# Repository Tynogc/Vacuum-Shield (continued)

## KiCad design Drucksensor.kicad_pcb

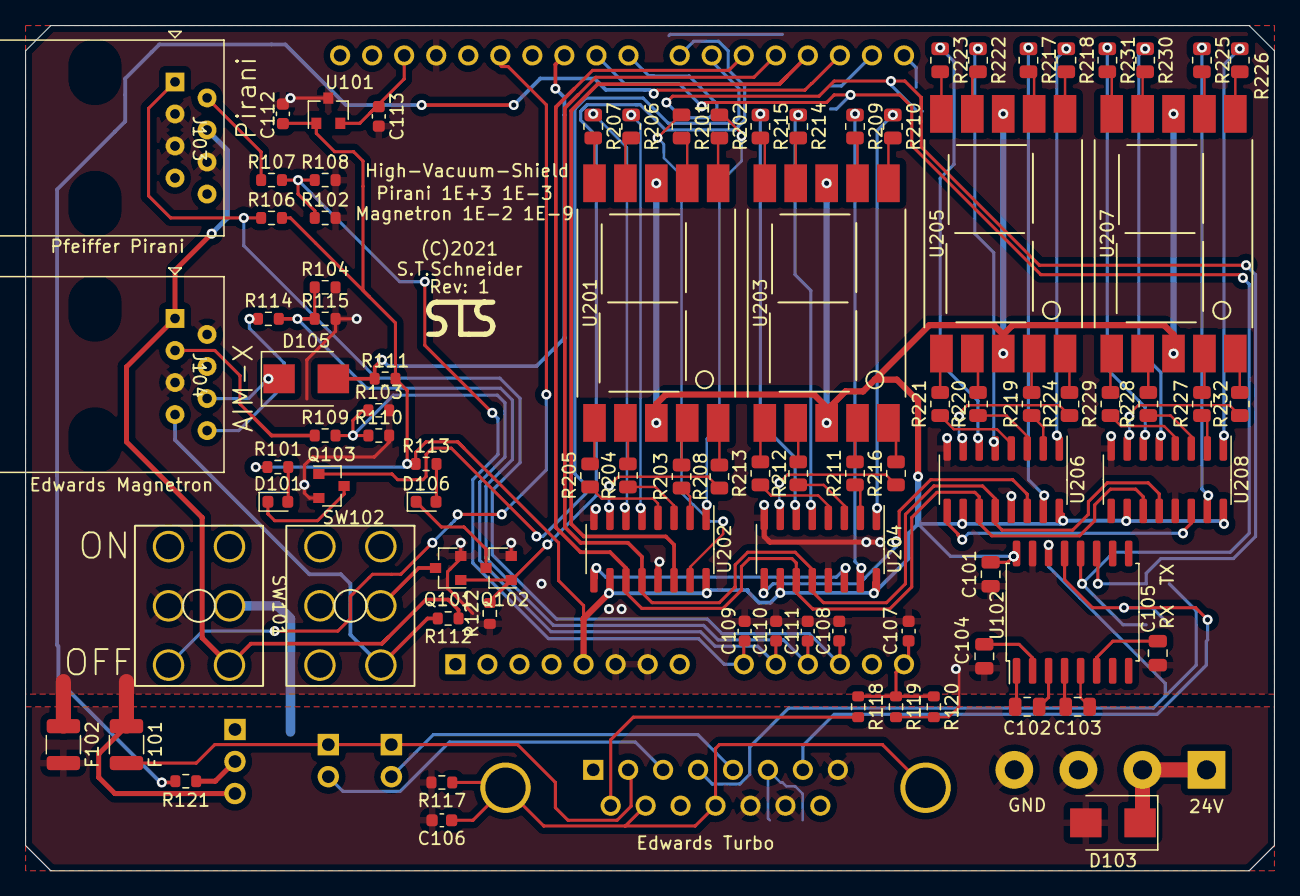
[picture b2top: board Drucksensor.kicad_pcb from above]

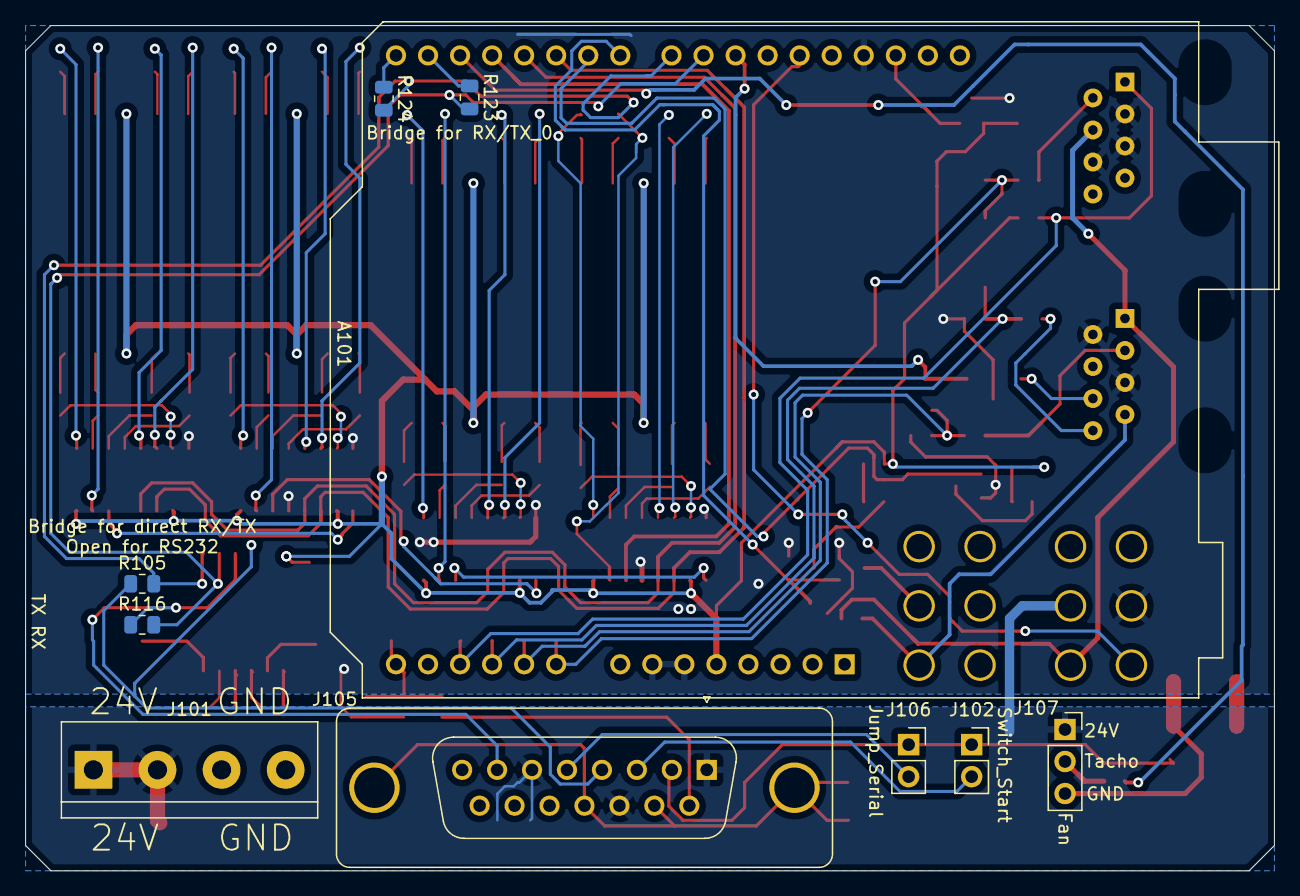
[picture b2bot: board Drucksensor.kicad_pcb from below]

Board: 2 copper layers, 99.0 x 67.0 mm, 98 parts (10 on the bottom side), 114 nets.

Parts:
A101: Arduino_UNO_R3
C101, C102, C103, C104, C105: 1µ 16V; C_0805_2012Metric
C106, C107, C108, C109, C110, C111, C112, C113: 100n; C_0603_1608Metric
D101, D106: grün; LED_0603_1608Metric
D103, D105: STPS340U; D_SMB
F101, F102: Fuse; R_1210_3225Metric
J101: Conn_01x02; TerminalBlock_bornier-4_P5.08mm
J102: Start; PinSocket_1x02_P2.54mm_Vertical
J103, J104: RJ45; RJ45_Amphenol_54602_mod
J105: DB15_Female_MountingHoles; DSUB-15_Female_Vertical_P2.77x2.84mm_MountingHoles
J106: Serial; PinSocket_1x02_P2.54mm_Vertical
J107: Conn_01x03_Male; PinSocket_1x03_P2.54mm_Vertical
Q101, Q102, Q103: Q_NMOS_GSD; SOT-23
R101, R113: 470; R_0603_1608Metric
R102, R103, R104, R106, R107, R108, R109, R110, R111, R114, R115, R118, R119, R120, R122: 10k; R_0603_1608Metric
R105, R116, R123, R124: Open; R_0805_2012Metric
R112: NC; R_0603_1608Metric
R117, R121: 10; R_0603_1608Metric
R201, R202, R203, R204, R205, R206, R207, R208, R209, R210, R211, R212, R213, R214, R215, R216, R217, R218, R219, R220, R221, R222, R223, R224, R225, R226, R227, R228, R229, R230, R231, R232: R; R_0805_2012Metric
SW101: SW_DPST; Switch_DPDT
SW102: SW_SPDT; Switch_DPDT
U101: REF3040; SOT-23
U102: MAX232; SOIC-16W_7.5x10.3mm_P1.27mm
U201, U203, U205, U207: KCSA02-106; 7SEGMENT-LED__HDSM531_HDSM533_SMD
U202, U204, U206, U208: 74HC595; SOIC-16_3.9x9.9mm_P1.27mm

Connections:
+5V: A101.5 (+5V), C101.2, C112.2, R101.1, R106.2, R111.2, R113.1, U101.1 (IN), U102.16 (VCC), U201.3 (CA), U201.8 (CA), U202.10 (~SRCLR), U202.16 (VCC), U203.3 (CA), U203.8 (CA), U204.10 (~SRCLR), U204.16 (VCC), U205.3 (CA), U205.8 (CA), U206.10 (~SRCLR), U206.16 (VCC), U207.3 (CA), U207.8 (CA), U208.10 (~SRCLR), U208.16 (VCC)
+24V: J103.4, J104.1, R112.1, SW101.3
/7SegClk: A101.20 (D5), U202.11 (SRCLK), U204.11 (SRCLK), U206.11 (SRCLK), U208.11 (SRCLK)
/7SegData: A101.18 (D3), U202.14 (SER)
/7SegEN: A101.19 (D4), U202.12 (RCLK), U204.12 (RCLK), U206.12 (RCLK), U208.12 (RCLK)
/24_Ext: D103.1 (K), J101.1, J105.1, J105.6, J105.11 (P111), J107.1, SW101.2
/EnableAll: A101.21 (D6), Q103.1 (G)
/GND_Ref: F101.2, J102.1, J105.2, J106.1
/Magnetron_ADC: A101.10 (A1), C110.1, R103.1, R109.2, R110.1
/Magnetron_Enable: A101.22 (D7), Q101.1 (G), Q102.1 (G), R122.2
/Magnetron_Setpoint_ADC: A101.11 (A2), C111.1, R104.1, R114.2, R115.1
/Magnetron_Trip: A101.25 (D10), D105.2 (A), R111.1
/Main_ON: A101.27 (D12), SW101.6
/Pirani_ADC: A101.9 (A0), C109.1, R102.1, R107.2, R108.1
/Pirani_Ident: A101.12 (A3), C108.1, J103.1, R106.1
/PumpAnalog: J105.9, R118.2
/PumpAnalog_5V: A101.14 (SCL/A5), C107.1, R118.1, R119.1, R120.1
/RS232_RX: J105.7, R116.1, U102.13 (R1IN)
/RS232_TX: J105.4, R105.1, U102.14 (T1OUT)
/RX: A101.16 (D1/TX), R123.1
/RX_2: A101.24 (D9), R116.2, R123.2, U102.12 (R1OUT)
/Serial: J105.5, J106.2
/Start: J102.2, J105.3
/TX: A101.15 (D0/RX), R124.1
/TX_2: A101.23 (D8), R105.2, R124.2, U102.11 (T1IN)
/Tacho: A101.17 (D2), R121.1
Earth: C106.1, J105.0 (PAD), J105.10, J105.12, R117.1
GND: A101.6 (GND), A101.7 (GND), A101.29 (GND), C101.1, C104.2, C105.2, C107.2, C108.2, C109.2, C110.2, C111.2, C112.1, C113.2, F101.1, F102.1, J103.3, J103.5, J103.6, J104.2, J104.5, J107.3, Q101.2 (S), Q102.2 (S), Q103.2 (S), R102.2, R103.2, R104.2, R108.2, R110.2, R115.2, R119.2, R120.2, R122.1, SW101.5, U101.3 (GND), U102.15 (GND), U202.8 (GND), U202.13 (~OE), U204.8 (GND), U204.13 (~OE), U206.8 (GND), U206.13 (~OE), U208.8 (GND), U208.13 (~OE)
GNDPWR: C106.2, D103.2 (A), F102.2, J101.2, J105.8, J105.13, J105.14, R117.2
unnamed: A101.30 (AREF), C113.1, U101.2 (OUT)
unnamed: C102.1, U102.3 (C1-)
unnamed: C102.2, U102.1 (C1+)
unnamed: C103.1, U102.5 (C2-)
unnamed: C103.2, U102.4 (C2+)
unnamed: C104.1, U102.2 (VS+)
unnamed: C105.1, U102.6 (VS-)
unnamed: D101.1 (K), Q103.3 (D)
unnamed: D101.2 (A), R101.2
unnamed: D105.1 (K), J104.6
unnamed: D106.1 (K), Q102.3 (D)
unnamed: D106.2 (A), R113.2
unnamed: J103.2, R107.1
unnamed: J104.3, R109.1
unnamed: J104.7, R112.2, SW102.3 (C)
unnamed: J104.8, R114.1
unnamed: J107.2, R121.2
unnamed: Q101.3 (D), SW102.2 (B)
unnamed: R201.1, U202.15 (QA)
unnamed: R201.2, U201.7 (A)
unnamed: R202.1, U202.1 (QB)
unnamed: R202.2, U201.6 (B)
unnamed: R203.1, U202.2 (QC)
unnamed: R203.2, U201.4 (C)
unnamed: R204.1, U202.3 (QD)
unnamed: R204.2, U201.2 (D)
unnamed: R205.1, U202.4 (QE)
unnamed: R205.2, U201.1 (E)
unnamed: R206.1, U202.5 (QF)
unnamed: R206.2, U201.9 (F)
unnamed: R207.1, U202.6 (QG)
unnamed: R207.2, U201.10 (G)
unnamed: R208.1, U202.7 (QH)
unnamed: R208.2, U201.5 (DP)
unnamed: R209.1, U204.15 (QA)
unnamed: R209.2, U203.7 (A)
unnamed: R210.1, U204.1 (QB)
unnamed: R210.2, U203.6 (B)
unnamed: R211.1, U204.2 (QC)
unnamed: R211.2, U203.4 (C)
unnamed: R212.1, U204.3 (QD)
unnamed: R212.2, U203.2 (D)
unnamed: R213.1, U204.4 (QE)
unnamed: R213.2, U203.1 (E)
unnamed: R214.1, U204.5 (QF)
unnamed: R214.2, U203.9 (F)
unnamed: R215.1, U204.6 (QG)
unnamed: R215.2, U203.10 (G)
unnamed: R216.1, U204.7 (QH)
unnamed: R216.2, U203.5 (DP)
unnamed: R217.1, U206.15 (QA)
unnamed: R217.2, U205.7 (A)
unnamed: R218.1, U206.1 (QB)
unnamed: R218.2, U205.6 (B)
unnamed: R219.1, U206.2 (QC)
unnamed: R219.2, U205.4 (C)
unnamed: R220.1, U206.3 (QD)
unnamed: R220.2, U205.2 (D)
unnamed: R221.1, U206.4 (QE)
unnamed: R221.2, U205.1 (E)
unnamed: R222.1, U206.5 (QF)
unnamed: R222.2, U205.9 (F)
unnamed: R223.1, U206.6 (QG)
unnamed: R223.2, U205.10 (G)
unnamed: R224.1, U206.7 (QH)
unnamed: R224.2, U205.5 (DP)
unnamed: R225.1, U208.15 (QA)
unnamed: R225.2, U207.7 (A)
unnamed: R226.1, U208.1 (QB)
unnamed: R226.2, U207.6 (B)
unnamed: R227.1, U208.2 (QC)
unnamed: R227.2, U207.4 (C)
unnamed: R228.1, U208.3 (QD)
unnamed: R228.2, U207.2 (D)
unnamed: R229.1, U208.4 (QE)
unnamed: R229.2, U207.1 (E)
unnamed: R230.1, U208.5 (QF)
unnamed: R230.2, U207.9 (F)
unnamed: R231.1, U208.6 (QG)
unnamed: R231.2, U207.10 (G)
unnamed: R232.1, U208.7 (QH)
unnamed: R232.2, U207.5 (DP)
unnamed: U202.9 (QH'), U204.14 (SER)
unnamed: U204.9 (QH'), U206.14 (SER)
unnamed: U206.9 (QH'), U208.14 (SER)

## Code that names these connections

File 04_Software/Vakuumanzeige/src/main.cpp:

#include <Arduino.h>
#include <stdio.h>
//#include <Wire.h>
#include <SPI.h>

// Ausgänge
#define IndikatorLED PB0
#define Dimmer PB1
#define SSlatch PB2
#define RS485DE PD4
#define Pieper PD7

// ADCs
#define ID1 A0
#define ID2 A1
#define PSU_5V A2
#define PSU_24V A3
#define MESS1 A6
#define MESS2 A7


volatile uint16_t adcWerte[6][8]; // Speicherstelle für alle Daten vom ADC, 8 pro Quelle damit man sauber Gleitmittelwert rechnen kann

uint8_t lutZeichenGross[] = {
  0b11111010, // 0
  0b00110000, // 1
  0b11011001, // 2
  0b01111001, // 3
  0b00110011, // 4
  0b01101011, // 5
  0b11101011, // 6
  0b00111000, // 7
  0b11111011, // 8
  0b01111011, // 9
  0b10111011, // A
  0b11100011, // b
  0b11001010, // C
  0b11110001, // d
  0b11001011, // E
  0b10001011, // F
};

uint8_t lutZeichenKlein[] = {
  0b01111101, // 0
  0b01100000, // 1
  0b01010111, // 2
  0b01110110, // 3
  0b01101010, // 4
  0b00111110, // 5
  0b00111111, // 6
  0b01110000, // 7
  0b01111111, // 8
  0b01111110, // 9
  0b01111011, // A
  0b00101111, // b
  0b00011101, // C
  0b01100111, // d
  0b00011111, // E
  0b00011011, // F
};

typedef struct
{
  bool signGross;
  bool signKlein;
  uint8_t zeichenGross[4];
  uint8_t zeichenKlein[3];
  uint8_t dezPunktGross;
  uint8_t dezPunktKlein;
  uint16_t helligkeit;
  uint8_t plusMinus;
  uint8_t statusLeds;
} segments_t; 

typedef struct
{
  segments_t anzeige;
  uint8_t outputs;
  uint8_t inputs;
} shiftReg_t;

typedef struct 
{
  int16_t mantisse;
  int8_t exponent;
} miniFloat_t;

// Globale Variablen

segments_t siebenSegments;
shiftReg_t schieberegisterdaten;
miniFloat_t vakuumsensor_1;
miniFloat_t vakuumsensor_2;
miniFloat_t raumdruck;



void setup() {
  // put your setup code here, to run once:
  pinMode(IndikatorLED, OUTPUT);
  pinMode(Dimmer, OUTPUT);
  pinMode(SSlatch, OUTPUT);
  pinMode(RS485DE, OUTPUT);
  pinMode(Pieper, OUTPUT);

  // Peripherie!
  // ADC:
  ADCSRA = 1<<ADEN | 1<<ADIF | 1<<ADIE | 1<<ADPS2 | 1<<ADPS1 | 1<<ADPS0;
  ADCSRB = 0;

  // Serielle Schnittstelle:
  Serial.begin(9600);

  // Initialisiere Variablen
  analogWrite(Dimmer, 50);


}

void loop() {
  // put your main code here, to run repeatedly:
  digitalWrite(IndikatorLED, 1);
  delay(100);
  digitalWrite(IndikatorLED, 0);
  delay(900);
}




/*
ISR (ADC_vect, ISR_BLOCK) {
  static uint8_t varNummer = 0;

  // Auslesen!
  if (ADMUX <= 3) {
    adcWerte[ADMUX][varNummer] = ADC;
  } else {
    adcWerte[ADMUX-2][varNummer] = ADC;
  }

  // Wähle nächsten Kanal zur ADC-Messung
  switch (ADMUX & 0x0f) {
    case 0:
    ADMUX = 1;
    break;

    case 1:
    ADMUX = 2;
    break;

    case 2:
    ADMUX = 3;
    break;

    case 3:
    ADMUX = 6;
    break;

    case 6: 
    ADMUX = 7;
    break;

    case 7: 
    ADMUX = 0;
    if (varNummer == 8) {
      varNummer = 0;
    } else {
      varNummer++;
    }

    default:
    ADMUX = 0;
    varNummer = 0;
  }
  ADCSRA |= 1<<ADSC; // Start.
}
*/



void ssSchieber(bool stat) {
  if (stat) {
    digitalWrite(SSlatch, 1);
  } else {
    digitalWrite(SSlatch, 0);
  }
}

void send74hc (uint8_t *txData, uint8_t *rxData, uint8_t len) {
  // sende und empfange Daten mit der HW-SPI Schnittstelle
  SPI.beginTransaction(SPISettings(10000000, MSBFIRST, SPI_MODE0));
  ssSchieber(0);

  for (uint8_t i = 0; i<len; i++) {
    rxData[i] = SPI.transfer(txData[i]);
  }

  ssSchieber(1);
  SPI.endTransaction();
}

int miniFloatToSegments(miniFloat_t *zahl, segments_t *anzeige) {
  if (abs(zahl->exponent) > 99 ) {
    return -1;
  }
  if (abs(zahl->mantisse) > 999 ) {
    return -1;
  }

  // lege Zeichen von Zahl in Anzeige ab. 


  return 0; // 0 ist ok
}

void updateAnzeige (segments_t *anzeige, uint8_t outputs, uint8_t *adr) {
  analogWrite(Dimmer, anzeige->helligkeit);
  uint8_t temp[7];
  uint8_t devAdr[7];
  
  temp[0] = anzeige->plusMinus | (anzeige->statusLeds)<<3;
  temp[1] = anzeige->zeichenKlein[1];
  temp[2] = anzeige->zeichenKlein[0];
  temp[3] = anzeige->zeichenGross[2];
  temp[4] = anzeige->zeichenGross[1];
  temp[5] = anzeige->zeichenGross[0];
  temp[6] = outputs;

  send74hc(temp, devAdr, 7);
  *adr = devAdr[0]; // es wird nur das erste Datenfeld sinnvoll gefüllt, danach kommen Nullen.
}

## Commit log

2021-09-19 Deleted Backups
2021-09-21 Zweiten Wiederstand zu Spannungsteiler hinzugefügt.
2021-09-21 RS232 hinzugefügt
2021-09-22 Anschluss für Edwards-Turbopumpe hinzugefügt
2021-09-22 Lüfter Eingefügt
2021-09-22 Silkscreen angepasst (Lüfter)
2021-09-23 Software-Serial für RS232 interface
2021-09-23 Flächen angepasst
2021-09-24 Kondensatoren für V-Ref
2021-10-16 Andere Werte für spannungsteiler
2021-10-17 Fertigungsdaten und IBOM hinzugefügt
2023-01-01 Lastenheft und Dokument für Materialbeschaffung hinzugefügt
2023-01-01 Ordnerstruktur aufgeräumt
2023-01-01 Datenblätter verwendeter und einiger geplanter Bauteile hinzugefügt
2023-01-01 Lastenheft erweitert und päsizisert. weitere kicad backup-Datei zur ignore hinzugefügt
2023-01-02 Spannungskurvenwerte hinzugefügt, Lastenheft angepasst
2023-01-02 Dimming jetzt OC1A
2023-01-11 Anzeigeplan weiter, Datenblatt der 0,56" Anzeige dazugefügt
2023-01-18 Neue Datenblätter von Röhren hinzugefügt
2023-01-18 Beschreibungsdatei aktualisiert
2023-01-22 Schaltplan Main erweitert und PSU/Ausgänge hinzugefügt
2023-01-22 Magnetron Datenblätter hinzugefügt
2023-01-22 Datenblätter von RS485 trx, Flash und AIM-Röhre hinzugefügt
2023-01-22 Schaltplan erweitert, I2C eingebaut
2023-01-22 ADC-Verwendung Betriebsspannungsmessung hinzugefügt
2023-01-22 I2C Pullups hinzugefügt
2023-01-22 Datenblätter APG und TPS54202 hinzugefügt
2023-01-22 Röhreneingänge angelegt
    Messröhren sind jetzt mit Edwards-Gängiger Beschaltung angelegt.
2023-01-23 Schaltwandler für 5V und Linearwandler für 3,3V angelegt
2023-01-23 Fenster geschlossen - Statusdatei
2023-01-23 RJ45-Anschlüsse überarbeitet
2023-01-23 Datenblatt 3,3V Linearwandler hinzugefügt
2023-01-25 TVS Dioden für Signal und DS18b20 hinzugefügt
2023-02-02 Pfeiffer IKR270 hinzugefügt
2023-03-03 Datenblätter der beiden LED-7-Segmente hinzugefügt
2023-03-03 Librarys für Schaltplansymbole Relais und LED-Segmente hinzugefügt
2023-03-03 Relais und Photomos eingefügt. TODO: Schraubklemmen!
2023-03-03 Anzeigen an bestellte Modelle angepasst
2023-03-03 Projektspezifische Libs eingefügt
2023-03-03 Reste von altem Projekt gelöscht und neue Daten, so fertig, eingefügt.
2023-03-03 Versionsänderungen 6.99 auf 7.0rc, Übergang alte Version 1 auf Version 2.dev
2023-03-04 Curve Fit Algo auf Spannungsteiler Detektion Sensor geworfen => 18,8k kamen raus. Jetzt wird es mal mit 18k probiert.
2023-03-04 BiDir 5V TVS Diode an ID Leitung Sensor angebracht
2023-03-14 Software angefangen - vscode und Platformio, mega328pb
2023-03-14 Datenblatt und Arduino-Beschreibung für den mega328pb hinzugefügt
2023-03-15 Folgende Änderungen wurden gelöscht und erneut durchgeführt UniDir 5V TVS Diode an ID Leitung Sensor angebracht Spannungsteiler Detektion Sensor => 18k
2023-07-02 kleine änderungen
2023-07-29 Layout weitergemacht, RJ45 Buchsen fehlen noch komplett
2023-11-24 Stecker fertig ausgewählt und Layout etwa 60% fertig
2023-11-24 RJ45-Plastikstecker hinzugefügt
2023-11-25 Layout aktuell fast DRC-Fehlerfrei, Überlappungen von Plus-Zeichen sind in Ordnung. Texte müssen noch ausgerichtet werden!
2023-11-25 Texte ausgerichtet.
2024-02-26 Software weitergemacht
